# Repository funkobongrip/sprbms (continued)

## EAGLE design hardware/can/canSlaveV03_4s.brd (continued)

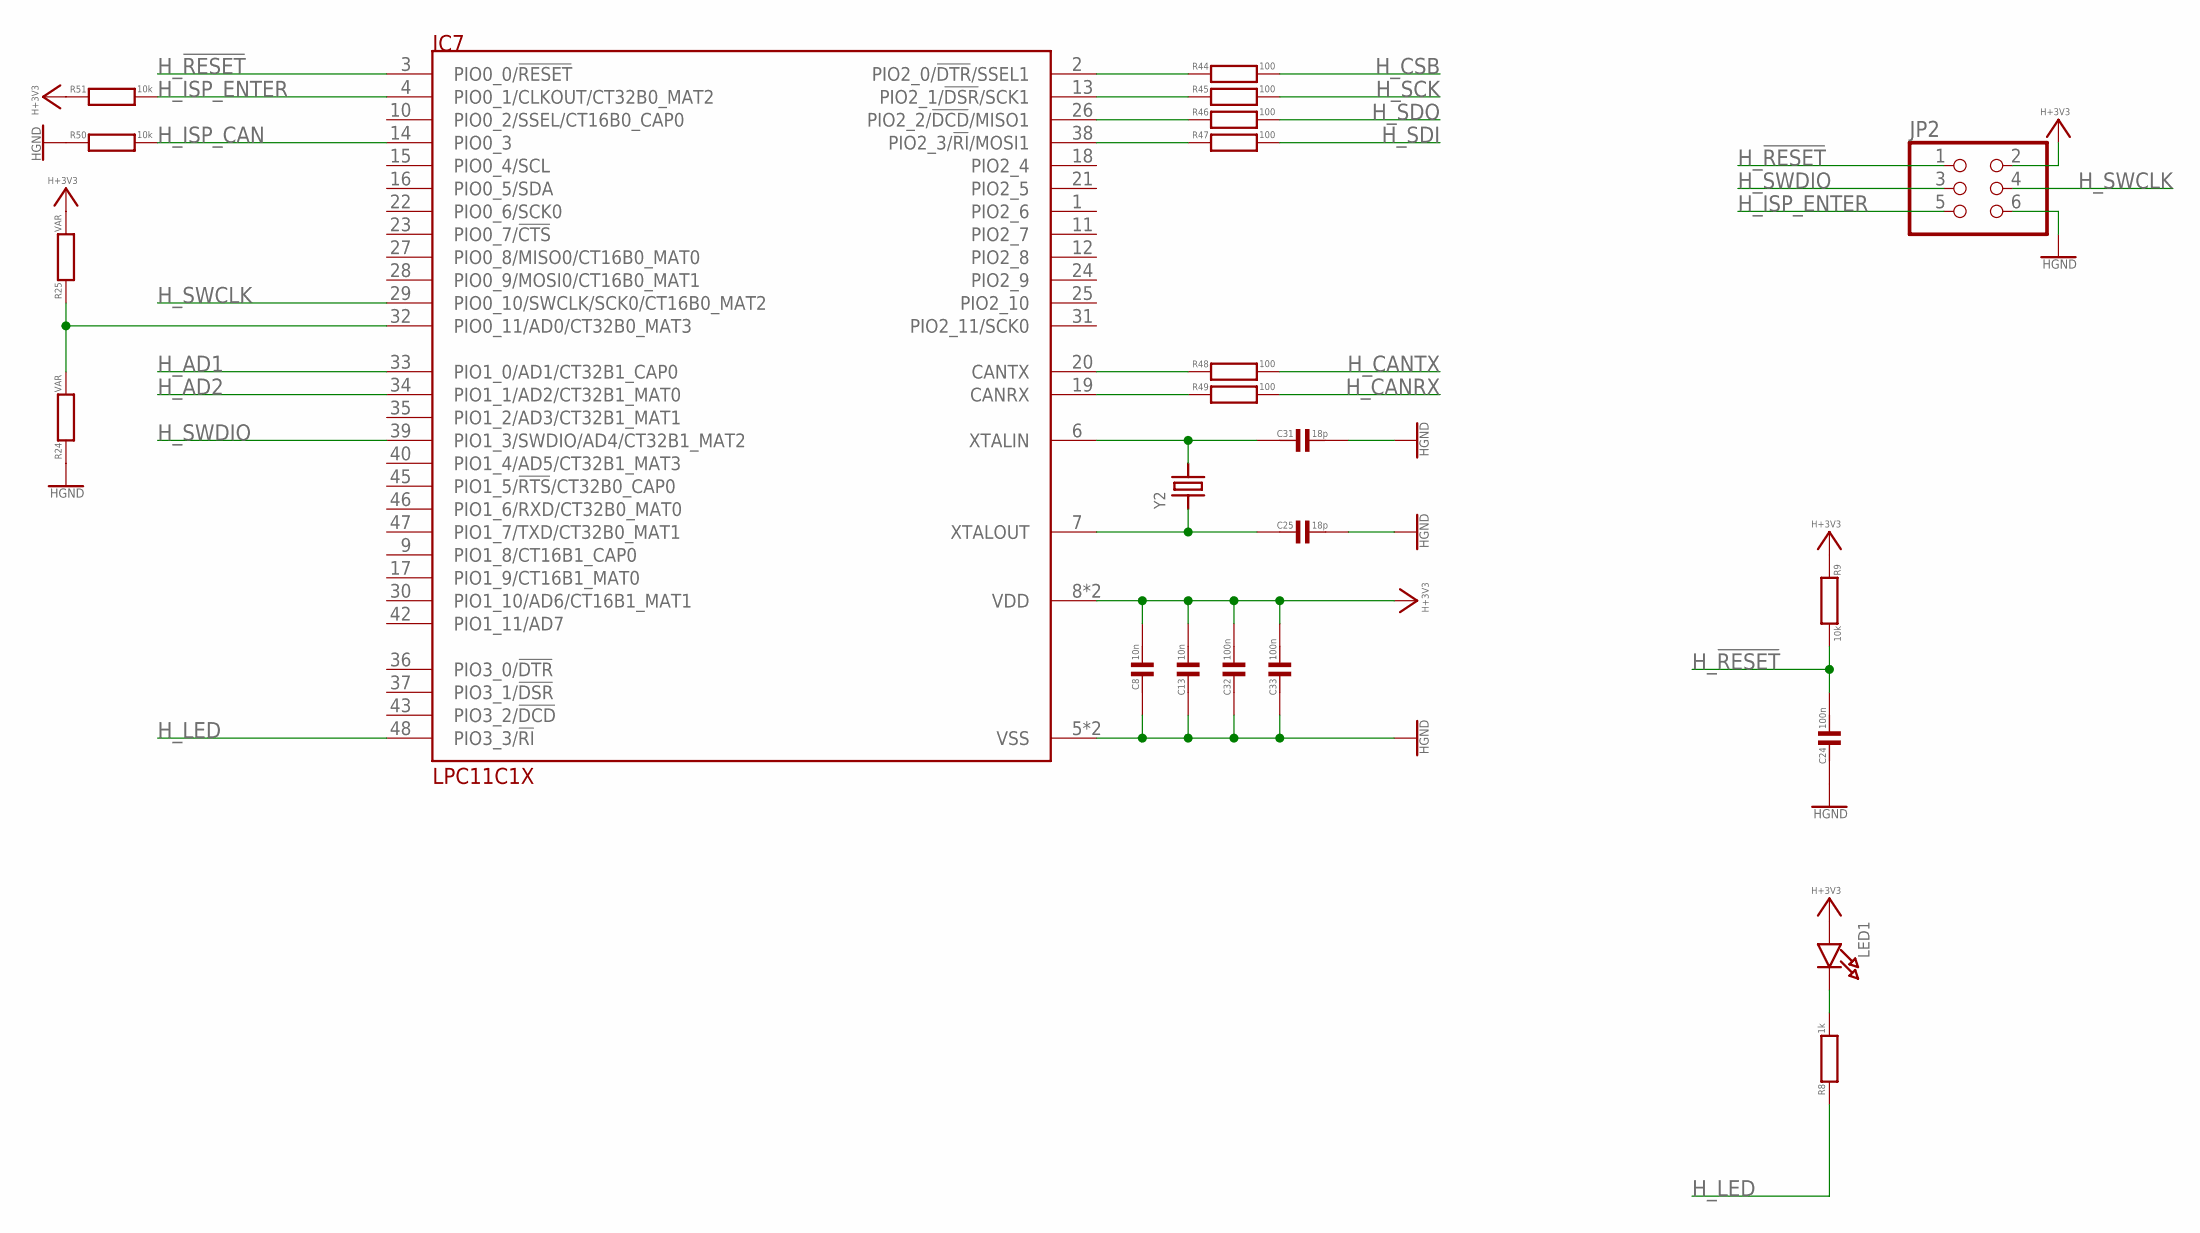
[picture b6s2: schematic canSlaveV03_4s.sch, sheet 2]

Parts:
C8, C13: 10n; C0603
C24, C32, C33: 100n; C0603
C25, C31: 18p; C0603
IC7: LPC11C1X; LQFP48
JP2: HEADER-2X31.27; 2X03_1.27MM_SMT
LED1: LED0603; CHIPLED_0603
R8: 1k; R0603
R9, R50, R51: 10k; R0603
R24, R25: VAR; R0603
R44, R45, R46, R47, R48, R49: 100; R0603
Y2: CRYSTALTHIN; CRYSTAL_3.2X2.5

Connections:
CANRX_U_H: IC7.19 (CANRX), R49.1
CANTX_U_H: IC7.20 (CANTX), R48.1
H+3V3: C8.1, C13.1, C32.1, C33.1, IC7.8 (VDD), IC7.44 (VDD), JP2.2, LED1.A, R9.1, R25.2, R51.1; also elsewhere on the board
HGND: C8.2, C13.2, C24.2, C25.1, C31.1, C32.2, C33.2, IC7.5 (VSS), IC7.41 (VSS), JP2.6, R24.1, R50.1; also elsewhere on the board
H_!RESET: C24.1, IC7.3 (PIO0_0/!RESET), JP2.1, R9.2
H_AD1: IC7.33 (PIO1_0/AD1/CT32B1_CAP0); also elsewhere on the board
H_AD2: IC7.34 (PIO1_1/AD2/CT32B1_MAT0)
H_ADR: IC7.32 (PIO0_11/AD0/CT32B0_MAT3), R24.2, R25.1
H_CANRX: R49.2; also elsewhere on the board
H_CANTX: R48.2; also elsewhere on the board
H_CSB: R44.2; also elsewhere on the board
H_ISP_CAN: IC7.14 (PIO0_3), R50.2
H_ISP_ENTER: IC7.4 (PIO0_1/CLKOUT/CT32B0_MAT2), JP2.5, R51.2
H_LED: IC7.48 (PIO3_3/!RI), R8.1
H_MISO: IC7.26 (PIO2_2/!DCD!/MISO1), R46.1
H_MOSI: IC7.38 (PIO2_3/!RI!/MOSI1), R47.1
H_SCK: R45.2; also elsewhere on the board
H_SCK1: IC7.13 (PIO2_1/!DSR!/SCK1), R45.1
H_SDI: R47.2; also elsewhere on the board
H_SDO: R46.2; also elsewhere on the board
H_SSEL: IC7.2 (PIO2_0/!DTR!/SSEL1), R44.1
H_SWCLK: IC7.29 (PIO0_10/SWCLK/SCK0/CT16B0_MAT2), JP2.4
H_SWDIO: IC7.39 (PIO1_3/SWDIO/AD4/CT32B1_MAT2), JP2.3
LED1C1: LED1.C, R8.2
XTALIN1: C31.2, IC7.6 (XTALIN), Y2.2
XTALOUT1: C25.2, IC7.7 (XTALOUT), Y2.1

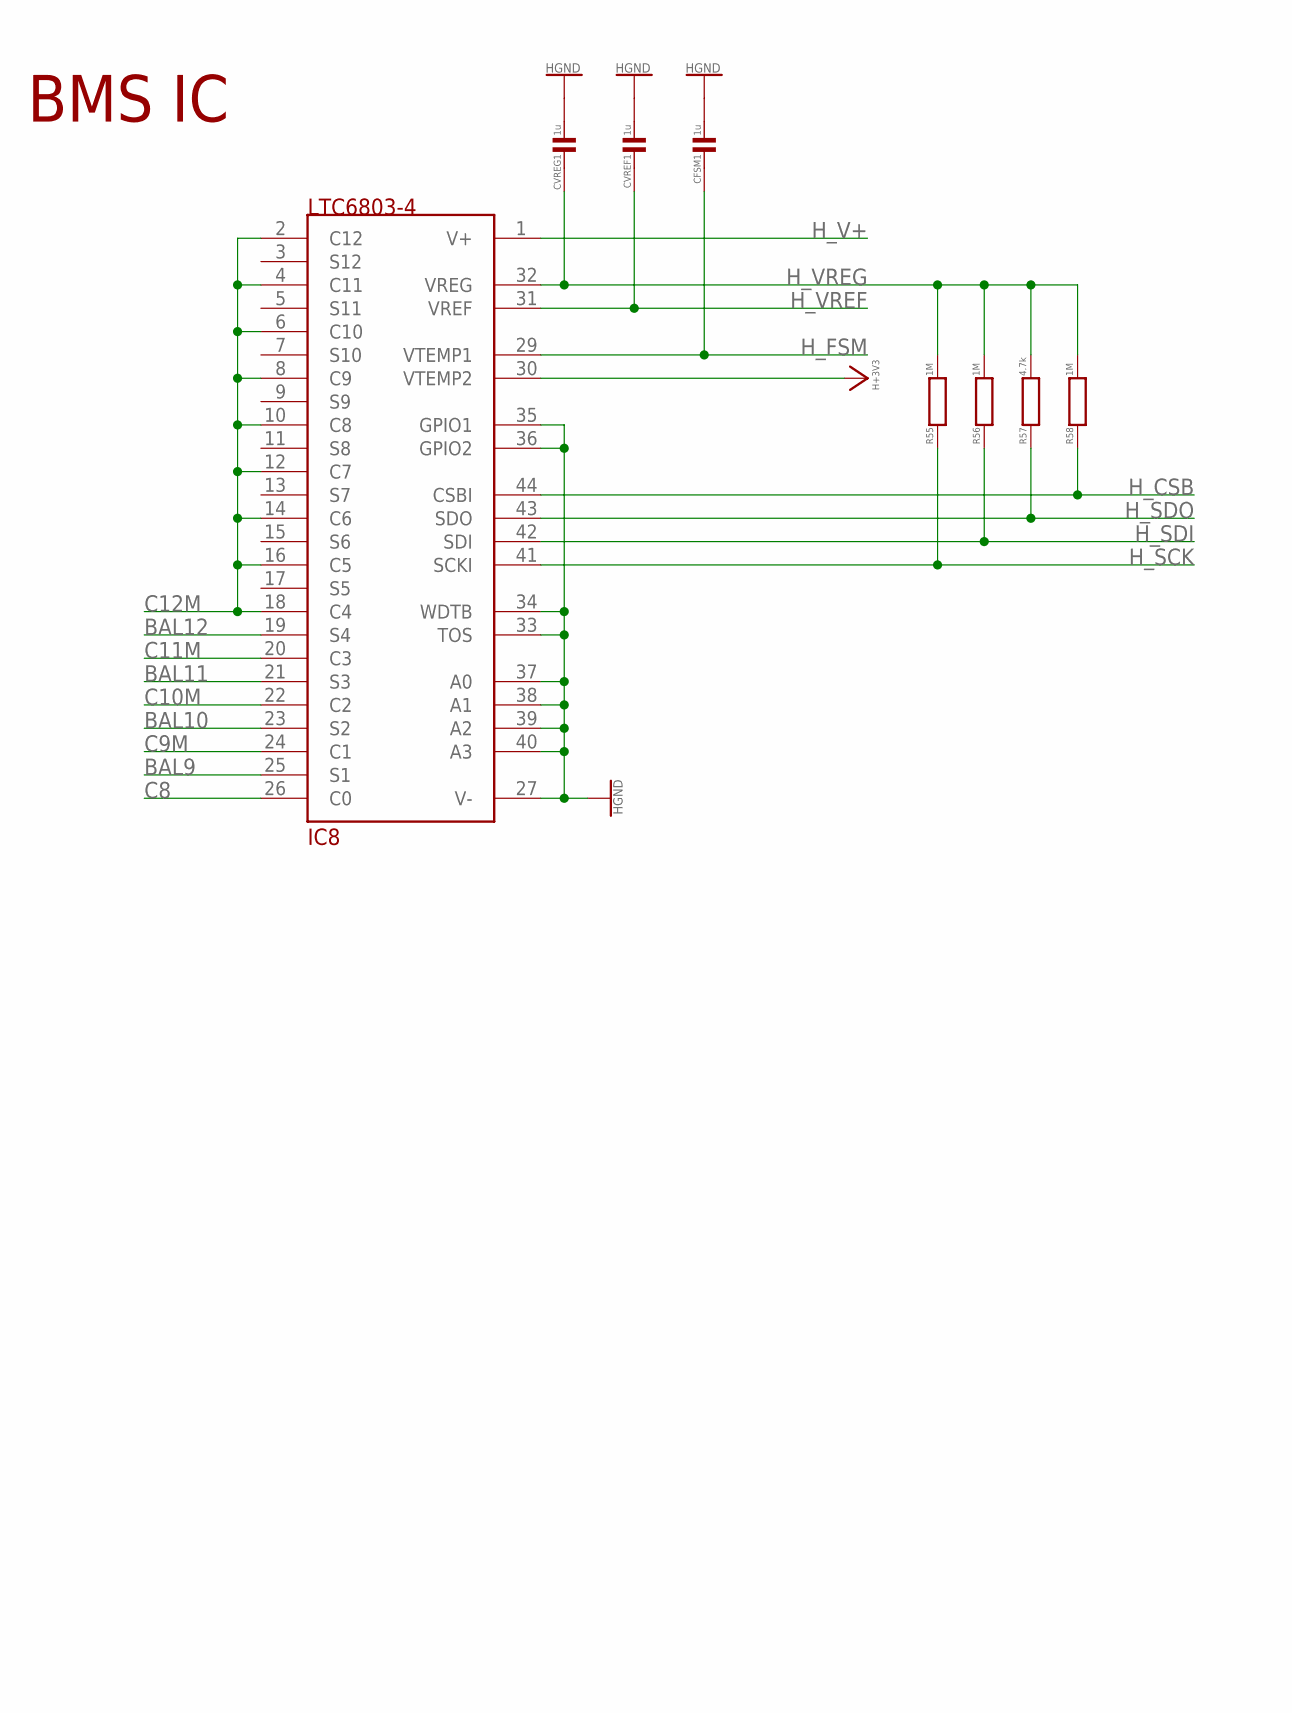
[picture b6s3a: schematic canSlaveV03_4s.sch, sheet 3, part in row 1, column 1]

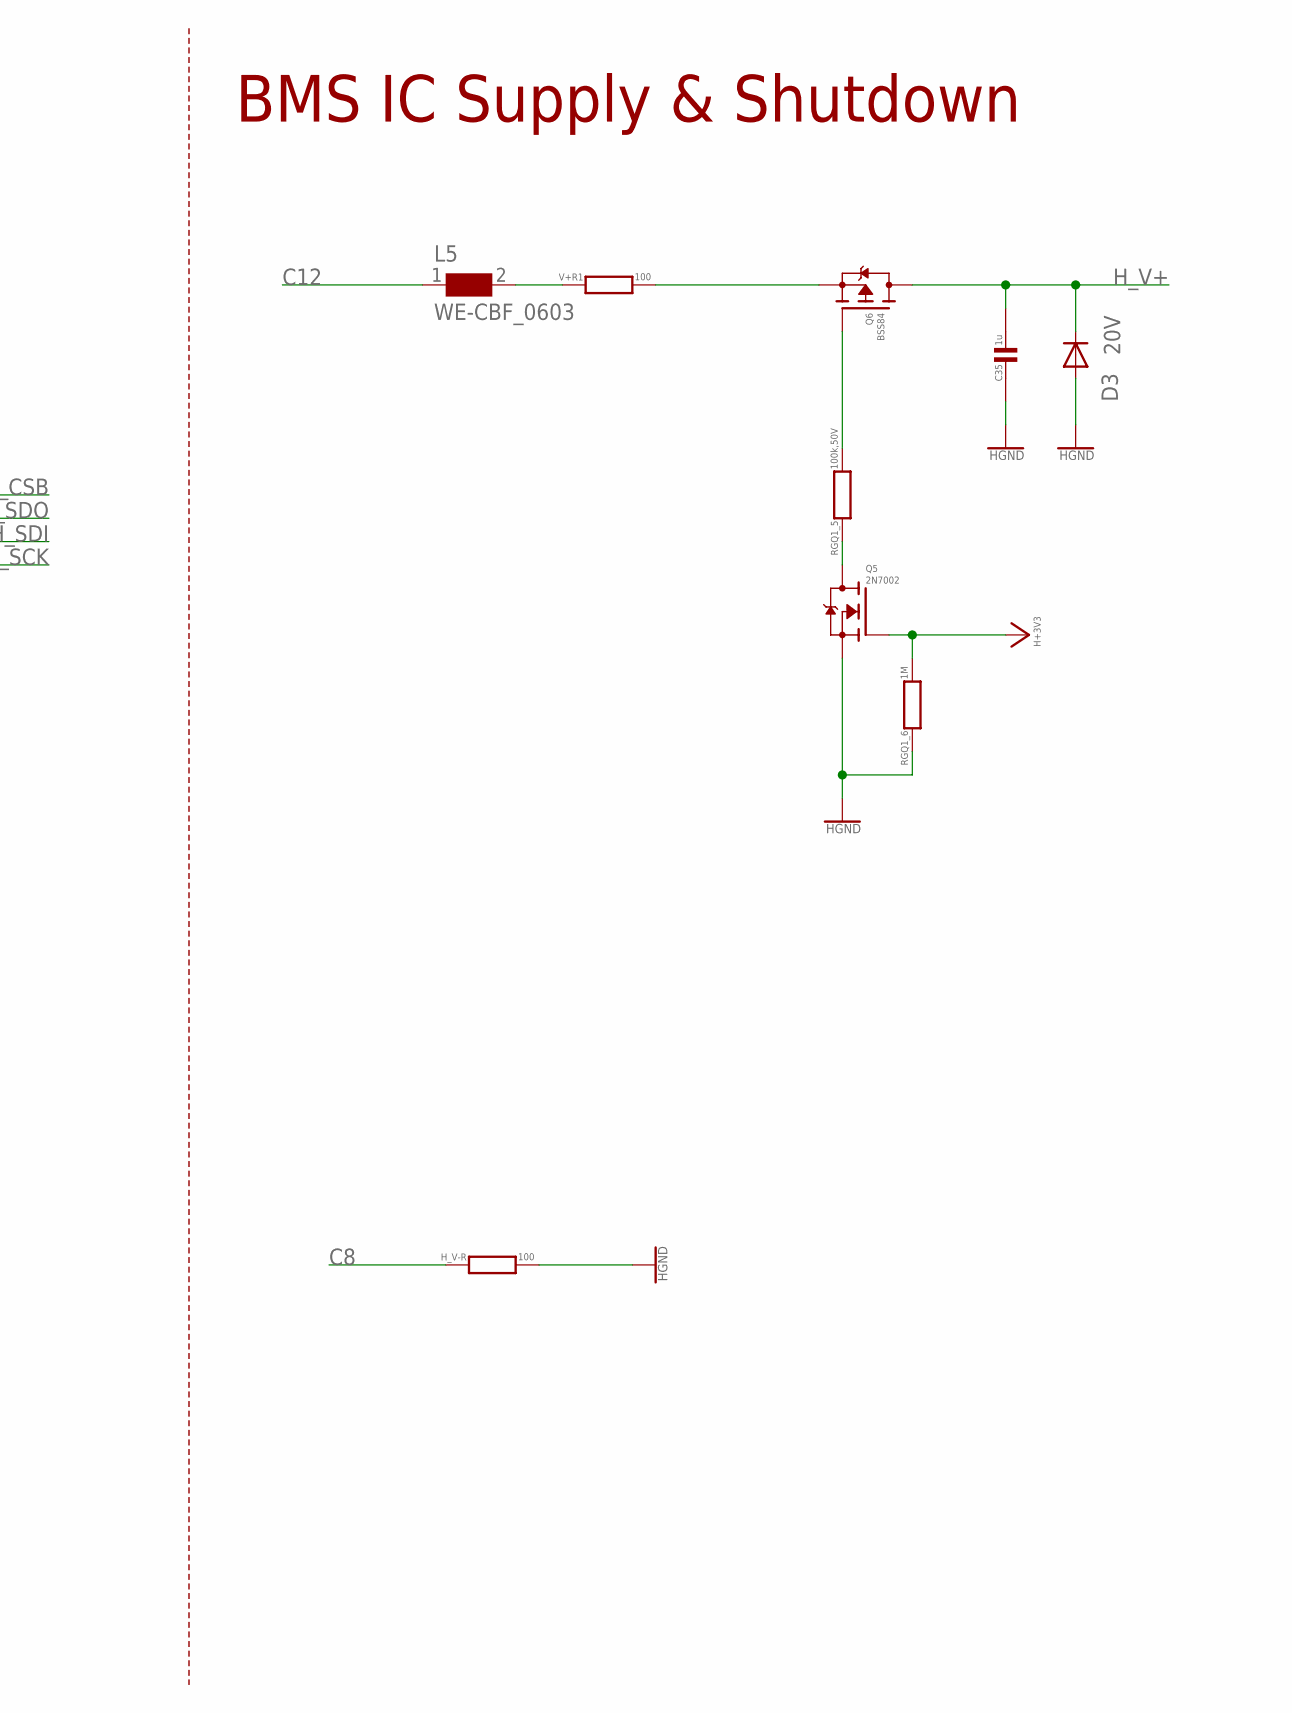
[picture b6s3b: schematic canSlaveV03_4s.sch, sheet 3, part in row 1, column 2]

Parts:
C35: 1u; C0603
CFSM1: 1u; C0603
CVREF1: 1u; C0603
CVREG1: 1u; C0603
D3: 20V; SOD323-R
H_V-R: 100; R0603
IC8: LTC6803-4; 44SSOP
L5: WE-CBF_0603; 0603
Q5: 2N7002; SOT23
Q6: BSS84; SOT23
R55, R56, R58: 1M; R0603
R57: 4.7k; R0603
RGQ1_5: 100k,50V; R0603
RGQ1_6: 1M; R0603
V+R1: 100; R0603

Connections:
BAL9: IC8.25 (S1); also elsewhere on the board
BAL10: IC8.23 (S2); also elsewhere on the board
BAL11: IC8.21 (S3); also elsewhere on the board
BAL12: IC8.19 (S4); also elsewhere on the board
C8: H_V-R.1, IC8.26 (C0); also elsewhere on the board
C9M: IC8.24 (C1); also elsewhere on the board
C10M: IC8.22 (C2); also elsewhere on the board
C11M: IC8.20 (C3); also elsewhere on the board
C12: L5.1; also elsewhere on the board
C12M: IC8.2 (C12), IC8.4 (C11), IC8.6 (C10), IC8.8 (C9), IC8.10 (C8), IC8.12 (C7), IC8.14 (C6), IC8.16 (C5), IC8.18 (C4); also elsewhere on the board
H+3V3: IC8.30 (VTEMP2), Q5.1 (G), RGQ1_6.2; also elsewhere on the board
HGND: C35.2, CFSM1.1, CVREF1.1, CVREG1.1, D3.A, H_V-R.2, IC8.27 (V-), IC8.33 (TOS), IC8.34 (WDTB), IC8.35 (GPIO1), IC8.36 (GPIO2), IC8.37 (A0), IC8.38 (A1), IC8.39 (A2), IC8.40 (A3), Q5.2 (S), RGQ1_6.1; also elsewhere on the board
H_CSB: IC8.44 (CSBI), R58.1; also elsewhere on the board
H_FSM: CFSM1.2, IC8.29 (VTEMP1); also elsewhere on the board
H_SCK: IC8.41 (SCKI), R55.1; also elsewhere on the board
H_SDI: IC8.42 (SDI), R56.1; also elsewhere on the board
H_SDO: IC8.43 (SDO), R57.1; also elsewhere on the board
H_V+: C35.1, D3.C, IC8.1 (V+), Q6.3 (D); also elsewhere on the board
H_VREF: CVREF1.2, IC8.31 (VREF)
H_VREG: CVREG1.2, IC8.32 (VREG), R55.2, R56.2, R57.2, R58.2
unnamed: Q5.3 (D), RGQ1_5.1
unnamed: L5.2, V+R1.1
Q1G1: Q6.1 (G), RGQ1_5.2
V+S1: Q6.2 (S), V+R1.2

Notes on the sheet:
BMS IC
BMS IC Supply & Shutdown

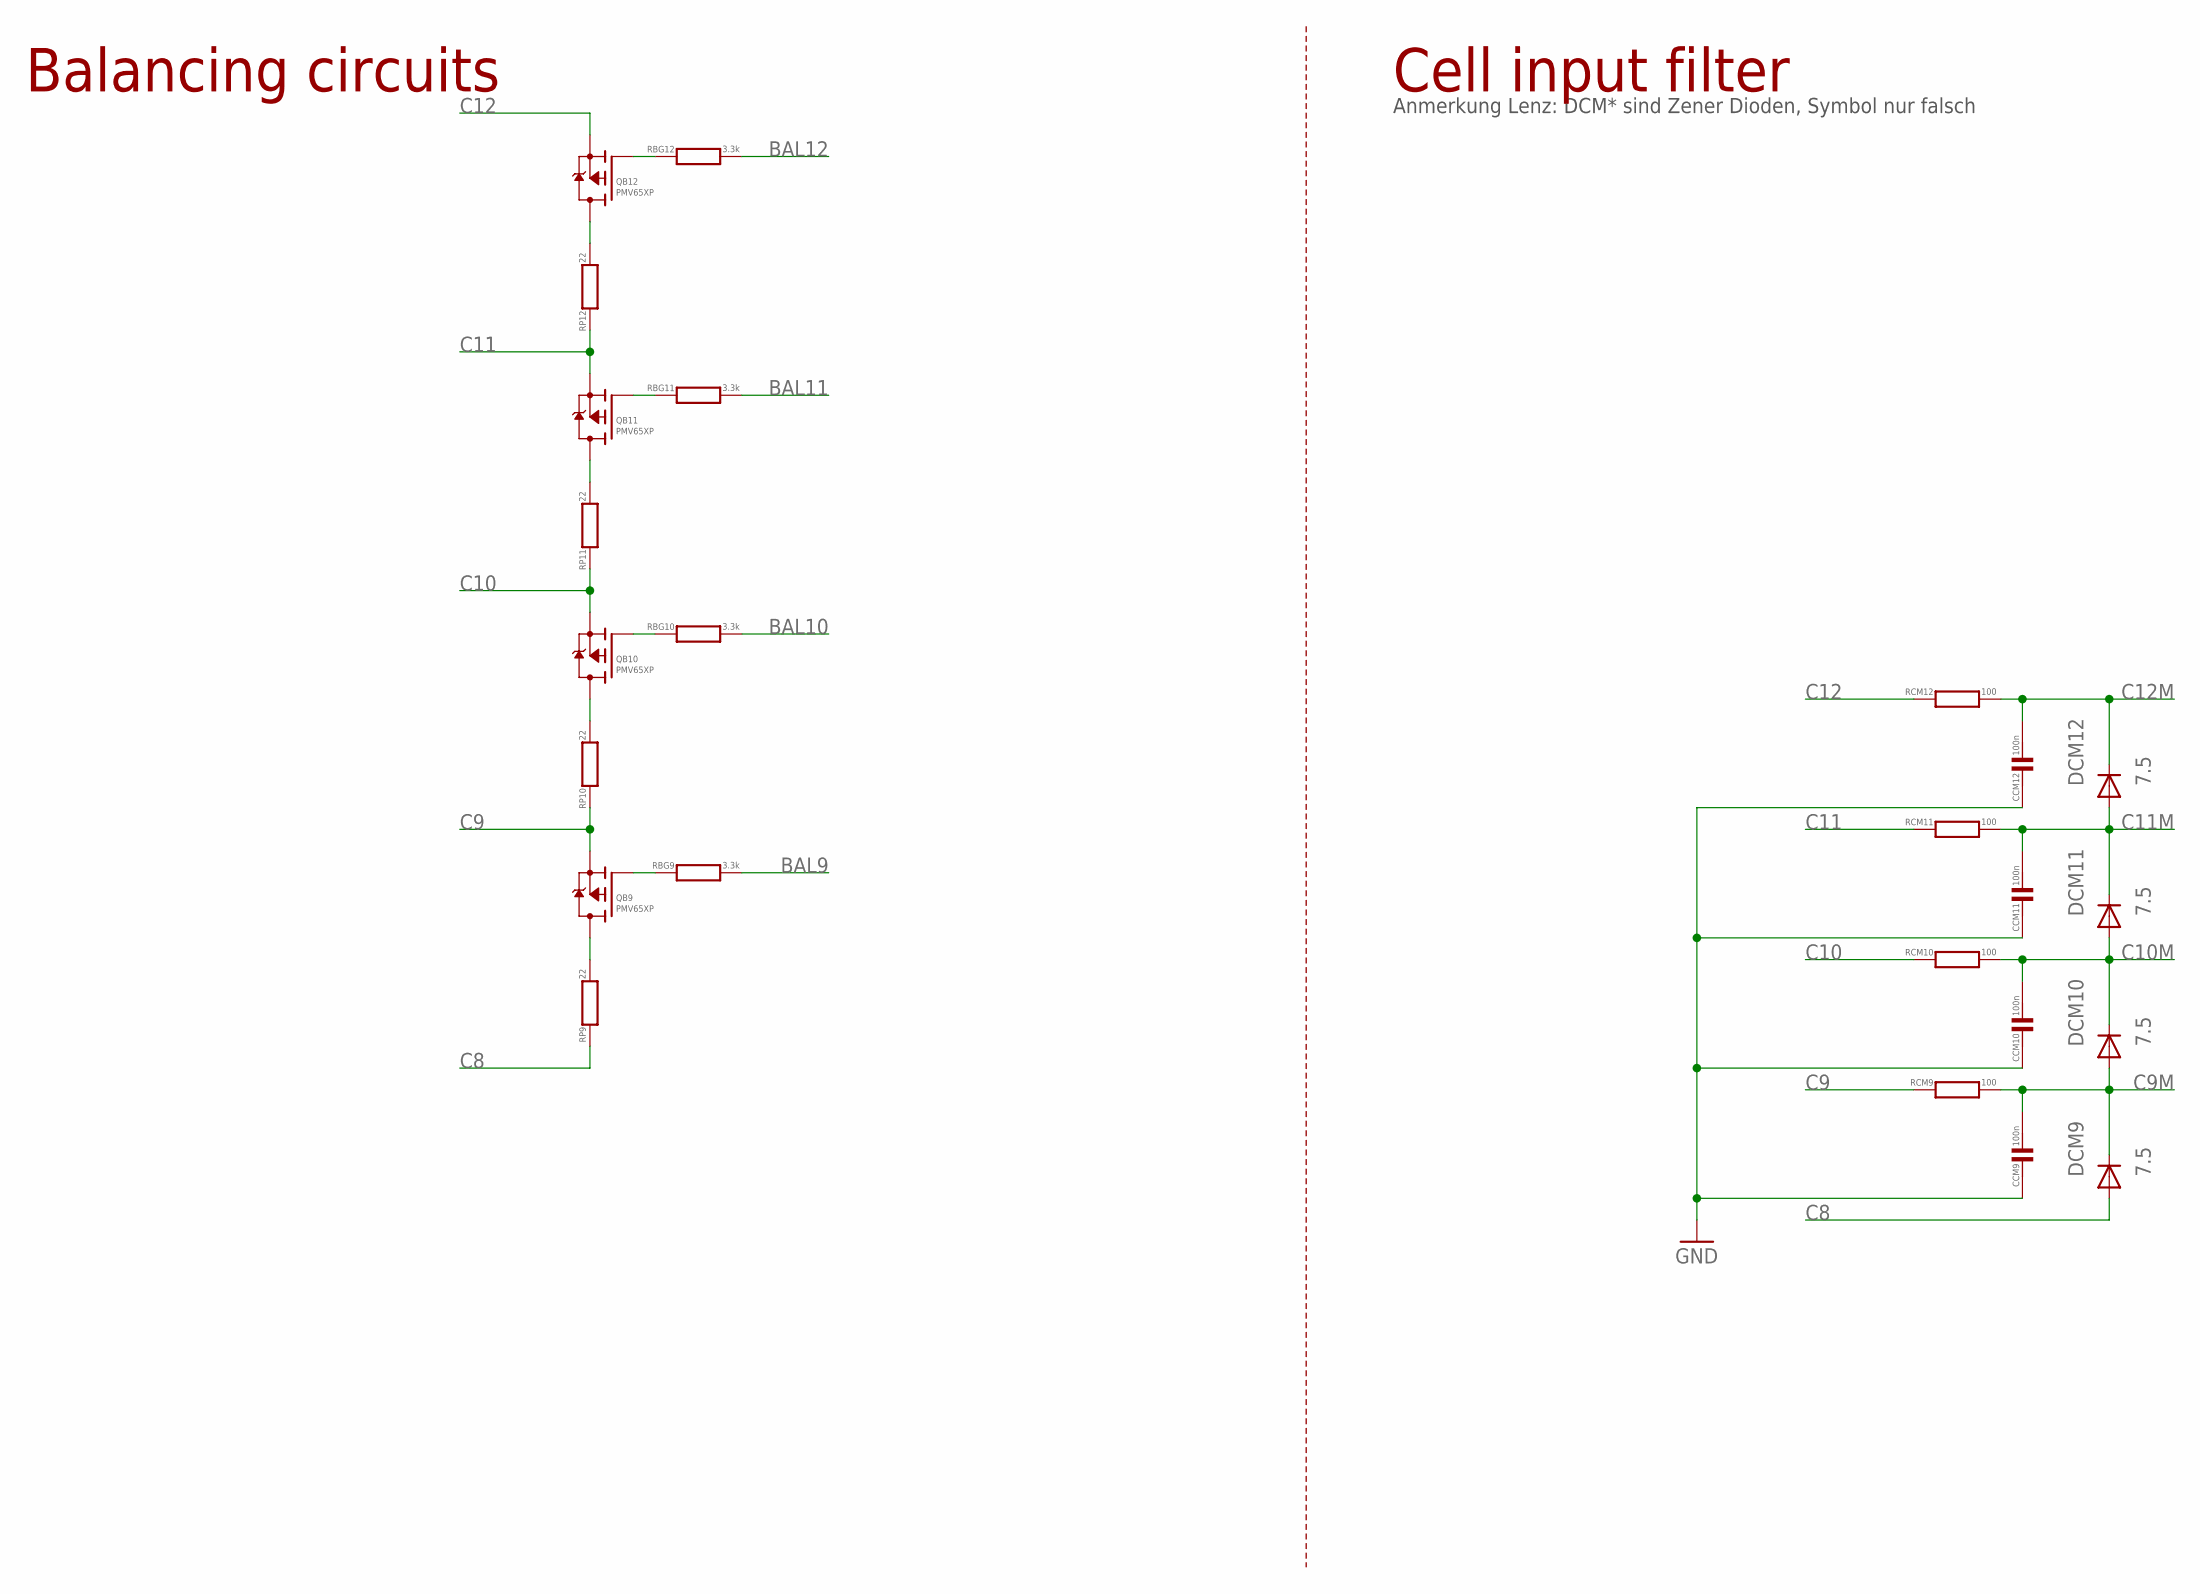
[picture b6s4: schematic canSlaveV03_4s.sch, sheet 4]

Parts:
CCM9, CCM10, CCM11, CCM12: 100n; C0603
DCM9, DCM10, DCM11, DCM12: 7.5; SOD323-R
QB9, QB10, QB11, QB12: PMV65XP; SOT23
RBG9, RBG10, RBG11, RBG12: 3.3k; R0603
RCM9, RCM10, RCM11, RCM12: 100; R0603
RP9, RP10, RP11, RP12: 22; R2512

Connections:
BAL9: RBG9.2; also elsewhere on the board
BAL10: RBG10.2; also elsewhere on the board
BAL11: RBG11.2; also elsewhere on the board
BAL12: RBG12.2; also elsewhere on the board
C8: DCM9.A, RP9.1; also elsewhere on the board
C9: QB9.2 (S), RCM9.1, RP10.1; also elsewhere on the board
C9M: CCM9.1, DCM9.C, DCM10.A, RCM9.2; also elsewhere on the board
C10: QB10.2 (S), RCM10.1, RP11.1; also elsewhere on the board
C10M: CCM10.1, DCM10.C, DCM11.A, RCM10.2; also elsewhere on the board
C11: QB11.2 (S), RCM11.1, RP12.1; also elsewhere on the board
C11M: CCM11.1, DCM11.C, DCM12.A, RCM11.2; also elsewhere on the board
C12: QB12.2 (S), RCM12.1; also elsewhere on the board
C12M: CCM12.1, DCM12.C, RCM12.2; also elsewhere on the board
CR9: QB9.3 (D), RP9.2
CR10: QB10.3 (D), RP10.2
CR11: QB11.3 (D), RP11.2
CR12: QB12.3 (D), RP12.2
HGND: CCM9.2, CCM10.2, CCM11.2, CCM12.2; also elsewhere on the board
QBG9: QB9.1 (G), RBG9.1
QBG10: QB10.1 (G), RBG10.1
QBG11: QB11.1 (G), RBG11.1
QBG12: QB12.1 (G), RBG12.1

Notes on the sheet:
Balancing circuits
Cell input filter
Anmerkung Lenz: DCM* sind Zener Dioden, Symbol nur falsch

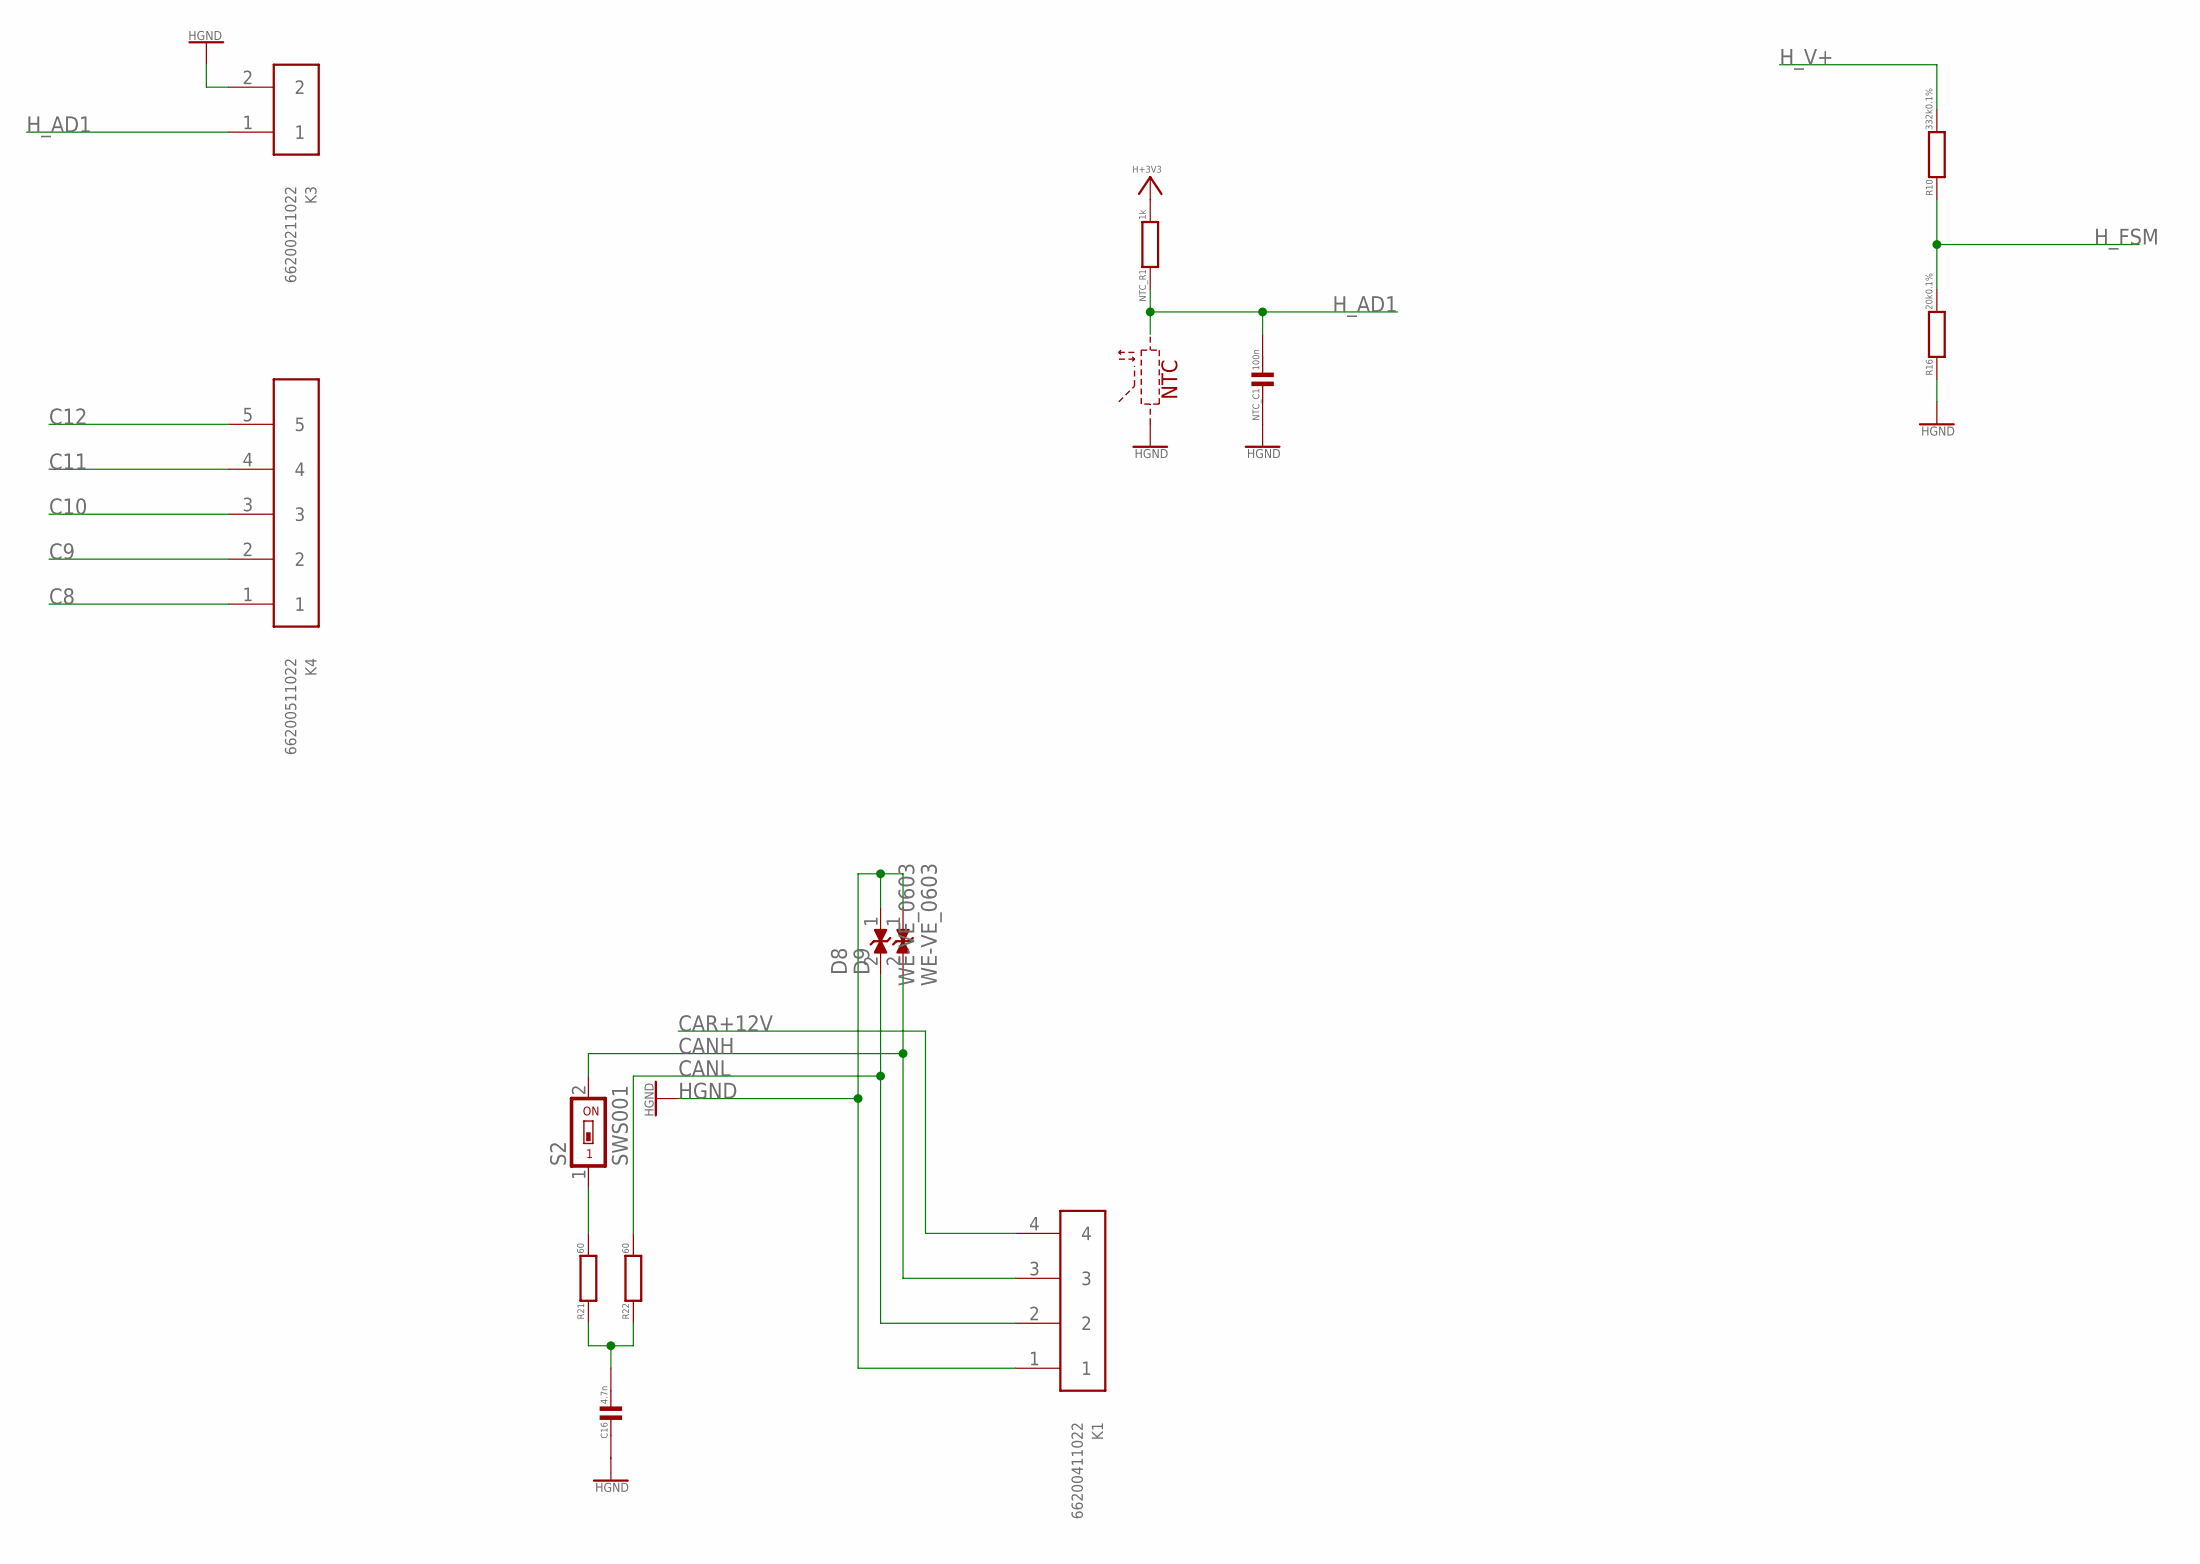
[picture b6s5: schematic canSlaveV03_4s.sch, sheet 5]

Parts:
C16: 4.7n; C0603
D8, D9: WE-VE_0603; WESURGE_0603
K1: 66200411022
K3: 66200211022
K4: 66200511022
NTC_C1: 100n; C0603
NTC_R1: 1k; R0603
R10: 332k0.1%; R0603
R16: 20k0.1%; R0603
R21, R22: 60; R0603
S2: SWS001; SMS-001

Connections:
C8: K4.1; also elsewhere on the board
C9: K4.2; also elsewhere on the board
C10: K4.3; also elsewhere on the board
C11: K4.4; also elsewhere on the board
C12: K4.5; also elsewhere on the board
CANH: D9.2, K1.3, S2.2; also elsewhere on the board
CANJ: R21.2, S2.1
CANL: D8.2, K1.2, R22.2; also elsewhere on the board
CANT: C16.1, R21.1, R22.1
CAR+12V: K1.4; also elsewhere on the board
H+3V3: NTC_R1.2; also elsewhere on the board
HGND: C16.2, D8.1, D9.1, K1.1, K3.2, NTC_C1.2, R16.1; also elsewhere on the board
H_AD1: K3.1, NTC_C1.1, NTC_R1.1; also elsewhere on the board
H_FSM: R10.1, R16.2; also elsewhere on the board
H_V+: R10.2; also elsewhere on the board

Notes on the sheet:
NTC

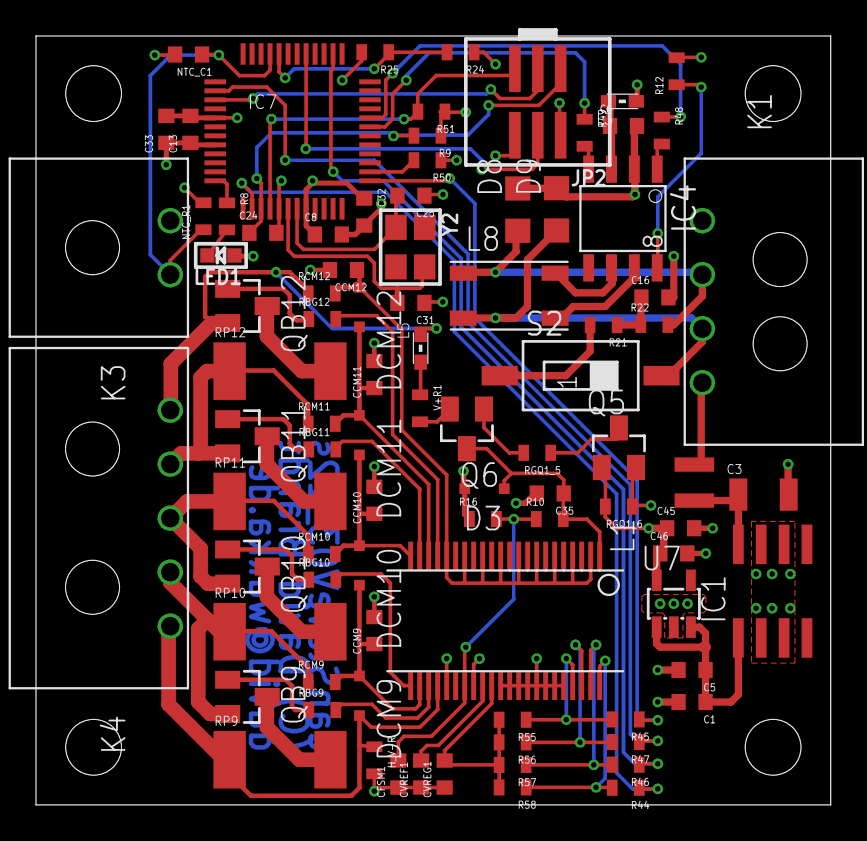
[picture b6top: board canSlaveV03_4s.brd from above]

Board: 4 copper layers, 44.2 x 42.7 mm, 90 parts (0 on the bottom side), 65 nets.

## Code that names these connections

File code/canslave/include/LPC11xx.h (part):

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  __IO uint32_t PIO0_1;                 /*!< Offset: 0x010 I/O configuration for pin PIO0_1/CLKOUT/CT32B0_MAT2 (R/W) */
  __IO uint32_t PIO1_8;                 /*!< Offset: 0x014 I/O configuration for pin PIO1_8/CT16B1_CAP0 (R/W) */
       uint32_t RESERVED1[1];
  __IO uint32_t PIO0_2;                 /*!< Offset: 0x01C I/O configuration for pin PIO0_2/SSEL0/CT16B0_CAP0 (R/W) */

  __IO uint32_t PIO2_7;                 /*!< Offset: 0x020 I/O configuration for pin PIO2_7 (R/W) */
  __IO uint32_t PIO2_8;                 /*!< Offset: 0x024 I/O configuration for pin PIO2_8 (R/W) */
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  __IO uint32_t PIO2_4;                 /*!< Offset: 0x040 I/O configuration for pin PIO2_4 (R/W) */
  __IO uint32_t PIO2_5;                 /*!< Offset: 0x044 I/O configuration for pin PIO2_5 (R/W) */
  __IO uint32_t PIO3_5;                 /*!< Offset: 0x048 I/O configuration for pin PIO3_5 (R/W) */
  __IO uint32_t PIO0_6;                 /*!< Offset: 0x04C I/O configuration for pin PIO0_6/SCK0 (R/W) */
  __IO uint32_t PIO0_7;                 /*!< Offset: 0x050 I/O configuration for pin PIO0_7/nCTS (R/W) */
  __IO uint32_t PIO2_9;                 /*!< Offset: 0x054 I/O configuration for pin PIO2_9 (R/W) */
  __IO uint32_t PIO2_10;                /*!< Offset: 0x058 I/O configuration for pin PIO2_10 (R/W) */
  __IO uint32_t PIO2_2;                 /*!< Offset: 0x05C I/O configuration for pin PIO2_2/DCD/MISO1 (R/W) */

  __IO uint32_t PIO0_8;                 /*!< Offset: 0x060 I/O configuration for pin PIO0_8/MISO0/CT16B0_MAT0 (R/W) */
  __IO uint32_t PIO0_9;                 /*!< Offset: 0x064 I/O configuration for pin PIO0_9/MOSI0/CT16B0_MAT1 (R/W) */
  __IO uint32_t SWCLK_PIO0_10;          /*!< Offset: 0x068 I/O configuration for pin SWCLK/PIO0_10/SCK0/CT16B0_MAT2 (R/W) */
  __IO uint32_t PIO1_10;                /*!< Offset: 0x06C I/O configuration for pin PIO1_10/AD6/CT16B1_MAT1 (R/W) */
  __IO uint32_t PIO2_11;                /*!< Offset: 0x070 I/O configuration for pin PIO2_11/SCK0 (R/W) */
  __IO uint32_t R_PIO0_11;              /*!< Offset: 0x074 I/O configuration for pin TDI/PIO0_11/AD0/CT32B0_MAT3 (R/W) */
  __IO uint32_t R_PIO1_0;               /*!< Offset: 0x078 I/O configuration for pin TMS/PIO1_0/AD1/CT32B1_CAP0 (R/W) */
  __IO uint32_t R_PIO1_1;               /*!< Offset: 0x07C I/O configuration for pin TDO/PIO1_1/AD2/CT32B1_MAT0 (R/W) */
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
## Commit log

2013-05-31 Initial Commit from SPR Master Directory
2016-02-18 Added canslave and next generation master idea based on TMS570
